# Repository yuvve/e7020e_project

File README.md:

# Sea Breeze Clock

The Sea Breeze Clock provides ultimate comfort for deep sleepers. Featuring a built-in humidifier, temperature sensor displayed on screen, and a gentle wake-up vibration function, it is designed to help you start your day feeling refreshed as if you have woken up on a private island.

## Members

- Yuval Levy (yuvlev-1@student.ltu.se)
- Calle Rautio (calrau-1@student.ltu.se)
- Simon Larsson (simlar-0@student.ltu.se)

## Hardware Features

- Display
- Humidifier for sea effect
- Backup battery for RTC and alarm time
- Speaker
- User interface (encoder / button)
- Programming interface
- Temperature measurement
- Fan for (hamster sized) sea breeze effect
- USB MINI connection
- Haptic actuator for SUPER GENTLE WAKE
- Hard(ish) protective case for the board

## Functionality and SW features

Besides mandatory functionality the Final Countdown features:

- Set Clock with long push and alarm time with short push. Change of volume with rotary button on default screen.
- CLI can control temperature sensor, speaker volume, intensity of buzzer, and fan speed control from CLI, and everything else.
- Maybe additional features.

## Individual grading goals and contributions

### Yuval Levy
#### 3 
- Contribute to the mandatory goals
#### 4
- Backup battery (HW & SW)
- Haptic actuator (HW & SW)
#### 5 
- Speaker (HW & SW)
- Power optimization (SW)
- Humidifier HW

### Calle Rautio
#### 3 
- Contribute to the mandatory goals
#### 4
- Humidifier SW
- Fan HW
- Fan SW
- HW component optimization (fewer MOSFETS)
#### 5 
- Speaker (HW & SW)

### Simon Larsson
#### 3 
- Contribute to the mandatory goals
#### 4
- Backup battery (HW & SW)
- Temperature on display SW
- Rotary encoder HW
#### 5 
- Speaker (HW & SW)
- Rotary encoder SW
- Power optimization (SW)

## HW References

- [MCU (QDAA QFN40)](https://docs.nordicsemi.com/bundle/ps_nrf52833/page/keyfeatures_html5.html) (**included**)
- [I2C Display](https://se.farnell.com/midas/mdob128032gv-wi/oled-display-cob-128-x-32-pixel/dp/3407291)
- [Humidifier for sea effect]() **DATASHEET MISSING!** [application](https://media.discordapp.net/attachments/1330909785532403752/1331984447591157781/temp.jpg?ex=679c2c6f&is=679adaef&hm=88c490139144ee49c3b781ae197cfe645891c9c844eaf4aa021b754f39057ddf&=&format=webp&width=810&height=403) (**included**)
- [Holder for backup battery (CR2032)](https://se.rs-online.com/web/p/battery-holders/7188457?gb=s)
- [Miniature speaker](https://se.rs-online.com/web/p/miniature-speakers/2596233)
- [DAC and amplifier for the speaker](https://se.farnell.com/analog-devices/max98357aete-t/audio-power-amp-d-40-to-85deg/dp/2949165)
- [Haptic Actuator](https://se.farnell.com/pui-audio/hd-emc1203-lw20-r/dc-motor-3vdc-26ohm-12000rpm/dp/4411154)
- [Rotary encoder, preferably with built-in button](https://se.rs-online.com/web/p/mechanical-rotary-encoders/7377773) (**included**)
- [Push button for resetting the program]() (**included**, alternatives:  TE Connectivity 1825910-7,  Alps Alpine STTSKHHBS) (**included**)
- [Fan for wind effect](https://se.rs-online.com/web/p/axial-fans/2887621?gb=s) (hamster sized)
- [LED](https://se.rs-online.com/web/p/leds/2648165) (**included**)
- USB Mini (**included**)
- [Analog temperature sensor](https://www.digikey.se/sv/products/detail/epcos-tdk-electronics/B57891M0103K000/3500546) (**included**)
- Serial programming header (**included**)
- Serial communication header to host, over dev-kit VCP (**included**)
- Case made either of wood or 3D-printed
### Other Parts
- Schottky diode ZLLS500TA ([link1](https://se.rs-online.com/web/p/schottky-diodes-rectifiers/0155096?gb=s), [link2](https://se.rs-online.com/web/p/schottky-diodes-rectifiers/1219937?gb=s)) x 3 (3 per board)

## SW References

**Crates/dependencies used in the project:**

- **[heapless](https://crates.io/crates/heapless/0.7.16)** – Fixed-capacity collections  
- **[cortex-m](https://docs.rs/cortex-m)** – Low-level access to Cortex-M processors  
- **[cortex-m-rtic](https://crates.io/crates/cortex-m-rtic/1.1.4)** – Real-time interrupt-driven concurrency  
- **[cortex-m-rt](https://crates.io/crates/cortex-m-rt/0.7.3)** – Minimal runtime for Cortex-M  
- **[embedded-hal](https://crates.io/crates/embedded-hal/0.2.7)** – Hardware abstraction layer for embedded systems  
- **[panic-rtt-target](https://crates.io/crates/panic-rtt-target/0.2.0)** – RTT-based panic handler  
- **[panic-halt](https://crates.io/crates/panic-halt/1.0.0)** – Halts execution on panic  
- **[rtt-target](https://crates.io/crates/rtt-target/0.6.1)** – Real-time tracing for embedded devices  
- **[systick-monotonic](https://crates.io/crates/systick-monotonic/1.0.0)** – Monotonic timer using SysTick  
- **[dwt-systick-monotonic](https://crates.io/crates/dwt-systick-monotonic/1.0.0)** – Monotonic timer using DWT and SysTick  
- **[nb](https://crates.io/crates/nb/1.1.0)** – Non-blocking operations abstraction  
- **[usb-device](https://crates.io/crates/usb-device/0.3.2)** – USB stack for embedded systems  
- **[usbd-serial](https://crates.io/crates/usbd-serial/0.2.2)** – USB-to-serial converter  
- **[usbd-hid](https://crates.io/crates/usbd-hid/0.8.2)** – USB HID implementation  
- **[embedded-graphics](https://crates.io/crates/embedded-graphics/0.8.1)** – Graphics library for embedded displays  
- **[ssd1306](https://crates.io/crates/ssd1306/0.9.0)** – Driver for SSD1306 OLED displays  
- **[libm](https://crates.io/crates/libm/0.2.11)** – Math library for no_std environments  
- **[profont](https://crates.io/crates/profont/0.7.0)** – Monospace bitmap font for embedded graphics  
- **[nrf52833-hal](https://crates.io/crates/nrf52833-hal/0.18.0)** – HAL for nRF52833 microcontrollers

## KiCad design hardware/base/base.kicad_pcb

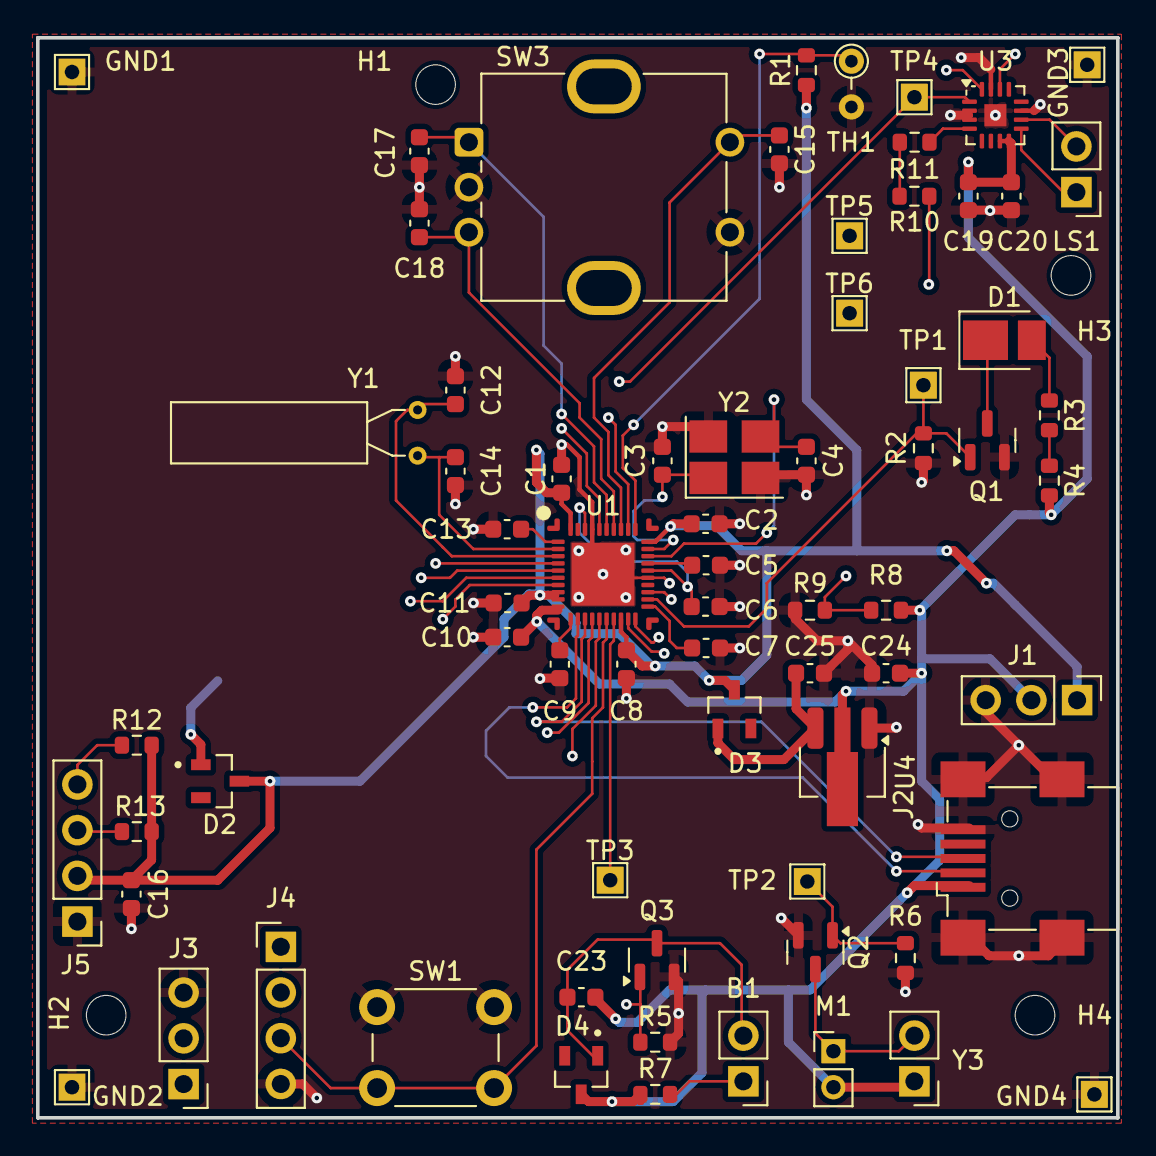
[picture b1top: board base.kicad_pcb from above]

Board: 4 copper layers, 60.0 x 60.0 mm, 75 parts (1 on the bottom side), 44 nets.

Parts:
B1: HD-EMC1203-LW20-R; PinHeader_1x02_P2.54mm_Vertical
BT1: Battery_Cell; TE_796136-1
C1, C6, C16: 1uF; C_0603_1608Metric
C2, C13: 100nF; C_0603_1608Metric
C3, C4, C12, C14: 12pF; C_0603_1608Metric
C5: 100pF; C_0603_1608Metric
C7: 820pF; C_0603_1608Metric
C8: 100nf; C_0603_1608Metric
C9: 4.7uf; C_0603_1608Metric
C10, C11: 4.7uF; C_0603_1608Metric
C15, C17, C18: 10nF; C_0603_1608Metric
C19: 0.1uF; C_0603_1608Metric
C20: 10uF; C_0603_1608Metric
C23: 0.1 uF; C_0603_1608Metric
C24, C25: 1.0 uF; C_0603_1608Metric
D1: LED; LED_PLCC_2835_Handsoldering
D2, D3, D4: D_Schottky_1_3; SOT91P240X110-3N
GND1, GND2, GND3, GND4: TestPoint; TestPoint_THTPad_1.5x1.5mm_Drill0.8mm
H1, H2, H3, H4: MountingHole; MountingHole_2.2mm_M2_ISO7380
J1: Debug; PinHeader_1x03_P2.54mm_Vertical
J2: USB_B_Mini; USB_Mini-B_Wuerth_65100516121_Horizontal
J3: Serial Interface; PinHeader_1x03_P2.54mm_Vertical
J4: SWD; PinHeader_1x04_P2.54mm_Vertical
J5: OLED Display; PinHeader_1x04_P2.54mm_Vertical
LS1: Speaker; PinHeader_1x02_P2.54mm_Vertical
M1: Fan_ALT; PinHeader_1x02_P2.00mm_Vertical
Q1, Q2, Q3: Q_NMOS_GSD; SOT-23
R1, R2, R5, R6, R12, R13: 10k; R_0603_1608Metric
R3, R4: 22; R_0603_1608Metric
R7: 22 Ohm; R_0603_1608Metric
R8: 68 kOhm; R_0603_1608Metric
R9: 100 kOhm; R_0603_1608Metric
R10: 150 kOhm; R_0603_1608Metric
R11: 470 kOhm; R_0603_1608Metric
SW1: SW_PUSH_6mm_H9.5mm
SW3: RotaryEncoder_Switch; RotaryEncoder_Bourns_Vertical_PEC12R-3x17F-Sxxxx
TH1: Thermistor_NTC; R_Axial_DIN0204_L3.6mm_D1.6mm_P2.54mm_Vertical
TP1, TP2, TP3, TP4, TP5, TP6: TestPoint; TestPoint_THTPad_1.5x1.5mm_Drill0.8mm
U1: nRF52833-QDxx; QFN-40-1EP_5x5mm_P0.4mm_EP3.6x3.6mm
U3: MAX98357A; TQFN-16-1EP_3x3mm_P0.5mm_EP1.23x1.23mm
U4: MCP1700x-330xxMB; SOT-89-3_Handsoldering
Y1: 32kHz; Crystal_AT310_D3.0mm_L10.0mm_Horizontal
Y2: 32MHz; Crystal_SMD_3225-4Pin_3.2x2.5mm_HandSoldering
Y3: 1.70 MHz; PinHeader_1x02_P2.54mm_Vertical

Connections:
+3.3V: C1.1, C2.1, C8.1, C11.1, C16.1, D2.3 (K), D3.3 (K), J1.1, J5.2, R1.1, R12.1, R13.1, U1.8 (VDD), U1.9 (VDDH), U1.18 (VDD), U1.30 (VDD), U1.40 (VDD)
/AMP_BCLK: TP5.1, U1.4 (P0.04/AIN2), U3.16 (BCLK)
/AMP_DIN: TP4.1, U1.36 (AIN7/P0.31), U3.1 (DIN)
/AMP_FAN_HUM: Q2.1 (G), R6.1, R10.1, TP2.1, U1.23 (NFC2/P0.10)
/AMP_LRCLK: TP6.1, U1.5 (P0.05/AIN3), U3.14 (LRCLK)
/DEC4_6: C6.2, U1.26 (DEC6), U1.38 (DEC4)
/DETECT_VSOURCE: R8.2, R9.1, U1.32 (AIN0/P0.02)
/HAPTIC: Q3.1 (G), R5.1, TP3.1, U1.17 (P0.20)
/LED: Q1.1 (G), R2.1, TP1.1, U1.22 (NFC1/P0.09)
/ROT_ENC_A: C17.1, SW3.A, U1.35 (AIN6/P0.30)
/ROT_ENC_B: C18.1, SW3.B, U1.34 (AIN5/P0.29)
/ROT_ENC_S1: C15.1, SW3.S1, U1.33 (AIN4/P0.28)
/VBUS: C10.1, C19.2, C20.2, C23.1, C24.1, D4.3 (K), J1.2, J2.1 (VBUS), M1.2 (-), R4.2, R7.1, R8.1, U1.10 (VBUS), U3.7 (VDD), U3.8 (VDD), U4.2 (VI), Y3.1
GND: BT1.2 (-), C1.2, C2.2, C3.1, C4.2, C5.2, C6.1, C7.1, C8.2, C9.2, C10.2, C11.2, C12.2, C13.2, C14.1, C15.2, C16.2, C17.2, C18.2, C19.1, C20.1, C24.2, C25.2, GND1.1, GND2.1, GND3.1, GND4.1, J1.3, J2.5 (GND), J2.6 (Shield), J3.3, J4.4, J5.1, Q1.2 (S), Q2.2 (S), Q3.2 (S), R2.2, R5.2, R6.2, R9.2, SW1.1, SW3.C, SW3.S2, TH1.2, U1.25 (VSS_PA), U1.37 (VSS), U1.41 (VSS), U3.2 (GAIN_SLOT), U3.3 (GND), U3.11 (GND), U3.15 (GND), U3.17 (PAD), U4.1 (GND), Y2.2, Y2.4
unnamed: B1.1, R7.2
unnamed: BT1.1 (+), D2.1 (A)
unnamed: D1.2 (A), R3.1
unnamed: D1.1 (K), Q1.3 (D)
unnamed: C25.1, D3.1 (A), U4.3 (VO)
unnamed: B1.2, C23.2, D4.1 (A), Q3.3 (D)
unnamed: J2.3 (D+), U1.13 (D+)
unnamed: J2.2 (D-), U1.12 (D-)
unnamed: J3.1, U1.14 (P0.15)
unnamed: J3.2, U1.15 (P0.17)
unnamed: J4.1, U1.20 (SWDCLK)
unnamed: J4.2, U1.19 (SWDIO)
unnamed: J4.3, SW1.2, U1.16 (P0.18/~RESET)
unnamed: J5.3, R13.2, U1.7 (P0.11)
unnamed: J5.4, R12.2, U1.6 (P1.09)
unnamed: M1.1 (+), Q2.3 (D), Y3.2
unnamed: R3.2, R4.1
unnamed: R10.2, R11.1
unnamed: R1.2, TH1.1, U1.31 (AIN1/P0.03)
unnamed: C13.1, U1.1 (DEC1)
unnamed: C5.1, U1.27 (DEC3)
unnamed: C7.2, U1.21 (DEC5)
unnamed: C9.1, U1.11 (DECUSB)
unnamed: C14.2, U1.2 (P0.00/XL1), Y1.2
unnamed: C12.1, U1.3 (P0.01/XL2), Y1.1
unnamed: C4.1, U1.28 (XC1), Y2.3
unnamed: C3.2, U1.29 (XC2), Y2.1
unnamed: LS1.2, U3.10 (OUTN)
unnamed: LS1.1, U3.9 (OUTP)
unnamed: R11.2, U3.4 (~SD_MODE)

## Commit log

2025-01-22 added files and wrote some basic things
2025-01-22 added more text
2025-01-22 mini!
2025-01-27 Added specific parts
2025-01-28 Add missing components and more TODO
2025-01-30 Finish dividing work
2025-01-30 Finish initial project description (#1)
    * added files and wrote some basic things
    * added more text
    * Update README.md
    * mini!
    * Update TODO.md
    * Update README.md
2025-01-30 Add assets
2025-01-30 Initial backup battery commit
2025-01-30 Add basic Schottky setup
    Missing footprints for diodes
2025-01-30 Update changelog
2025-01-31 Update goals
2025-01-31 add base schematic and rotary encoder
2025-01-31 fix display link
2025-01-31 add oled display
2025-01-31 add rotary encoder footprint
2025-02-01 add amplifier and speaker symbols
2025-02-02 opt and fan HW
2025-02-02 added change to changelog
2025-02-02 Rename backup_battery_hw to backup_battery
2025-02-02 Make library paths relative
2025-02-02 Add MCU to readme
2025-02-02 Specify MCU model in readme
2025-02-02 Add haptic actuator schematic
2025-02-02 Add humidifier circuit Requires higher voltage than available, might need adjustments
2025-02-02 Change label for consistency
2025-02-03 Update humidifier circuit
2025-02-03 Change transistor type for haptic actuator circuit
2025-02-03 Add PWR_FLAG to regulator circuit
2025-02-03 Add missing ground connections in regulator circuit
2025-02-03 combine components
2025-02-03 Replace transistor in haptic actuator circuit
2025-02-03 fix error
2025-02-03 Fix import paths for baseboard
2025-02-03 Change battery holder, add footprint and symbol
2025-02-03 update README, minor changes to schematic
2025-02-03 Add schematic (#2)
    * Add assets
    * Initial backup battery commit
    * Add basic Schottky setup
    Missing footprints for diodes
    * Update changelog
    * Update goals
2025-02-03 Add Schottky rectifier symbol and footprint
2025-02-03 import components to PCB
2025-02-03 Fix relative paths
2025-02-03 Change transducer symbol
2025-02-03 Update PCB and Schema after symbol change
2025-02-03 Remove separate schematics
2025-02-04 did some layout and routing
    CHANGELOG
2025-02-04 Changelog
2025-02-04 move humidifier to fan/SD_MODE control pin, small fixes
2025-02-04 Add diode footprint
2025-02-04 finished placing components
2025-02-04 fix references
2025-02-04 Add missing symbol
2025-02-04 Finish front layer traces
2025-02-04 Finish traces
    Few warnings left
2025-02-04 add mounting holes
2025-02-04 Finish first hardware iteration (#3)
    * Add Schottky rectifier symbol and footprint
    * import components to PCB
    * Fix relative paths
    * Change transducer symbol
    * Update PCB and Schema after symbol change
    * Remove separate schematics
2025-02-06 Add pull-up resistors to display
2025-02-26 blinking working
2025-02-26 Enable unsafe code denial
2025-02-26 Remove trace, clean up
2025-02-26 PWM dimmable LED working
2025-03-02 Reset button implemented
2025-03-02 Rotary encoder, interrupt handling and debouncing
2025-03-02 Rotary encoder push switch
2025-03-03 small fix
2025-03-03 Add proper UICR handling
2025-03-03 LED example (#4)
    * blinking working
    * Enable unsafe code denial
    * Remove trace, clean up
    * PWM dimmable LED working
    * Add proper UICR handling
    ---------
2025-03-04 added box design
2025-03-05 Move hw gitignore to hw folder
2025-03-05 State machine draft
2025-03-05 Add alarm WFI
2025-03-05 Remove states that were not really states
2025-03-05 Move hw gitignore to hw folder (#5)
2025-03-05 Add enum state machine
2025-03-05 Add missing steps value
2025-03-06 Add backup mode example
2025-03-06 Thermistor working
2025-03-06 Add interrupt counter
2025-03-06 Add main, launch tasks
2025-03-06 Improve testability
2025-03-07 Fix warnings, update measured vdd
2025-03-07 Backup mode working
2025-03-07 Add main, launch tasks (#7)
2025-03-07 Examples for reset button, rotary encoder and thermistor (#8)
    * blinking working
    * Enable unsafe code denial
    * Remove trace, clean up
    * PWM dimmable LED working
    * Reset button implemented
    * small fix
2025-03-07 Split into two examples
2025-03-07 Backup battery mode (#9)
    * Add backup mode example
    * Add interrupt counter
    * Improve testability
    * Backup mode working
    * Split into two examples
2025-03-07 Implement sending and receiving serial over USB
2025-03-08 RTC clock implemented
2025-03-08 Update comments for clarity
2025-03-08 Enable deny warnings
2025-03-09 Implement sending and receiving serial over USB (#10)
2025-03-09 RTC clock and alarm example (#11)
    * RTC clock implemented
    * Update comments for clarity
    * Enable deny warnings
2025-03-09 Fan controll done
2025-03-09 Updated changelog and TODO
2025-03-10 Git history hopefully fixed
2025-03-11 another attempt
2025-03-11 one more attempt
2025-03-11 divided up everything to make the looks more tight
2025-03-12 Fan_SW done (#12)
2025-03-12 Display_SW Done (#13)
    * divided up everything to make the locks more tight
    ---------
2025-03-13 Integrate RTC timer
2025-03-13 Refactor rtc to take shared context
2025-03-13 Move rtc interrupt handling
2025-03-13 add haptic actuator
2025-03-13 Add I2S basic configuration
2025-03-13 add haptic actuator example (#14)
    * add haptic actuator
    * Update CHANGELOG.md and TODO.md
2025-03-13 My attempt at speaker setup
2025-03-15 Got transfer to work, does not sound good
2025-03-17 Integrate pwm and led into state machine
2025-03-17 Move uicr handling
2025-03-17 Integrate thermistor
2025-03-17 Make PWM ramp up slower
2025-03-17 Integrate rotary encoder and reset button
2025-03-17 Cargo lock changes
2025-03-17 Integrate fan, humidifier and haptic actuator
    PWM sequence needs to be tested
2025-03-17 Initial display integration (un-tested)
2025-03-18 Add temperature limits
2025-03-18 CLI working
2025-03-18 Small fixes
2025-03-18 CLI time printing works
2025-03-18 Refactor GPIO pin initialization into a dedicated module
2025-03-18 Add cli (#15)
    * CLI working
    * CLI time printing works
    * Update changelog
2025-03-18 Small fixes for clarity, ran fmt
2025-03-18 Add individiual PWM sequences
2025-03-18 Fix incorrect wrapping around midnight
2025-03-18 Fix displayed time after setting
2025-03-18 Fix warnings
2025-03-18 Fix initial display update
2025-03-18 Add positional constants for display
2025-03-19 Updated Box Design
2025-03-19 more speaker examples
2025-03-19 Display fully working
2025-03-19 Remove commented code
2025-03-19 State machine integration (#16)
    * State machine draft
    * Add alarm WFI
    * Remove states that were not really states
    * Add enum state machine
    * Add missing steps value
    * Integrate RTC timer
2025-03-19 Updated TODO.md
2025-03-19 Updated CHANGELOG.md
2025-03-20 Fix fan example
2025-03-20 Fix fan example (#17)
2025-03-20 PWM example
2025-03-20 PWM example (#18)
2025-03-20 No more pain
2025-03-20 More pain
2025-03-20 Torture
2025-03-20 Speaker not working
2025-03-21 Last minute changes
2025-03-22 Final integration (#19)
    * No more pain
    * More pain
    * Torture
    * CLI working
    * Speaker not working
    * Last minute changes
